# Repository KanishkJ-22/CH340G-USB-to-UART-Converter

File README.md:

# CH340G USB to UART Converter PCB

USB to UART/TTL converter for programming and debugging microcontrollers.

## Overview
Converts USB protocol to simple serial (TX/RX) communication.
Allows any computer to communicate with UART-based microcontrollers.

## Specifications
- Input: USB Micro-B (5V from host)
- Output: TX, RX, VCC (5V), GND via 4-pin header
- Baud rates: up to 2Mbps
- Crystal: 12MHz for precise timing
- Protection: Polyfuse on VBUS

## Components
- U1: CH340G USB to UART IC (SOIC-16)
- J1: USB Micro-B connector
- J2: 4-pin output header (TX, RX, VCC, GND)
- Y1: 12MHz crystal oscillator
- F1: Polyfuse (500mA) — overcurrent protection
- C1: 10µF decoupling capacitor
- C2, C5: 100nF decoupling capacitors
- C3, C4: 22pF crystal load capacitors

## Pinout (J2 Output Header)
| Pin | Signal |
|-----|--------|
| 1 | TX |
| 2 | RX |
| 3 | VCC (5V) |
| 4 | GND |

## Tools 
- KiCad 9
- JLCPCB design rules
- Mixed SMD and through-hole components

## Notes
- Connect TX of this board to RX of target device
- Connect RX of this board to TX of target device
- Double-sided GND pour for noise reduction

## Files Provided
- /sch - Schematic of the PCB
- /kicad - KiCad project file
- /pcb - PCB view of the file
- /gerbers - Manufacturing files ready to be fabricated
- .png of the 3D representation

## Status
Fourth PCB project. First board with SMD components and USB interface.

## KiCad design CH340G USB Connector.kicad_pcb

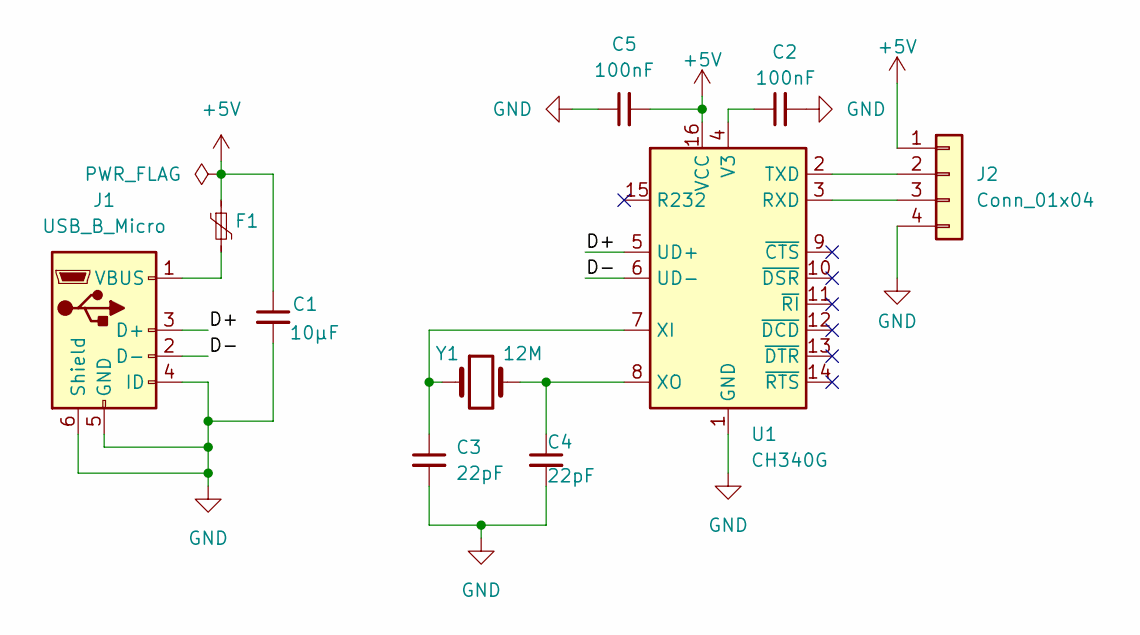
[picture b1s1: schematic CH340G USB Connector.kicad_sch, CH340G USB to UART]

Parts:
C1: 10μF; C_Radial_D5.0mm_H7.0mm_P2.00mm
C2, C5: 100nF; C_Disc_D3.0mm_W2.0mm_P2.50mm
C3, C4: 22pF; C_Disc_D3.0mm_W1.6mm_P2.50mm
F1: Fuse_1812_4532Metric
J1: USB_B_Micro; USB_Micro-B_Amphenol_10118194-0001LF_Horizontal
J2: Conn_01x04; PhoenixContact_GMSTBVA_2,5_4-G_1x04_P7.50mm_Vertical
U1: CH340G; SOIC-16_3.9x9.9mm_P1.27mm
Y1: 12M; Crystal_HC49-U_Vertical

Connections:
+5V: C1.1, C5.2, F1.1, J2.1 (VCC), U1.16 (VCC)
/D+: J1.3 (D+), U1.5 (UD+)
/D-: J1.2 (D-), U1.6 (UD-)
GND: C1.2, C2.2, C3.2, C4.2, C5.1, J1.4 (ID), J1.5 (GND), J1.6 (Shield), J2.4 (GND), U1.1 (GND)
unnamed: F1.2, J1.1 (VBUS)
unnamed: J2.3 (RXD), U1.3 (RXD)
unnamed: J2.2 (TXD), U1.2 (TXD)
unnamed: C2.1, U1.4 (V3)
unnamed: C3.1, U1.7 (XI), Y1.1
unnamed: C4.1, U1.8 (XO), Y1.2

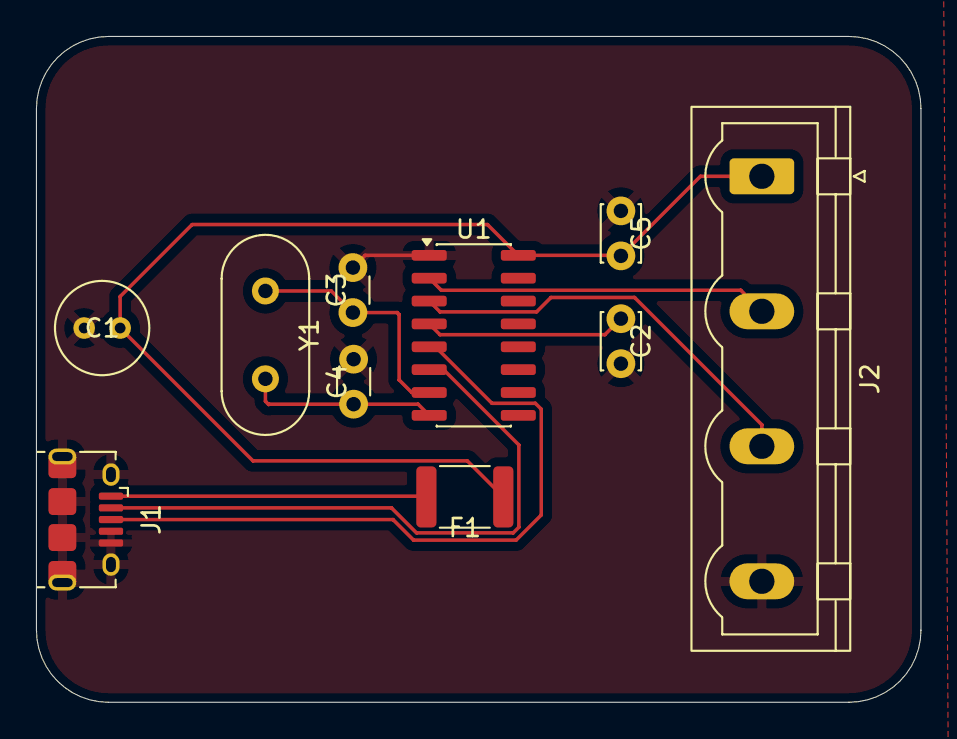
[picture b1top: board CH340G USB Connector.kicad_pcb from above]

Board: 2 copper layers, 49.1 x 37.0 mm, 10 parts (0 on the bottom side), 10 nets.
